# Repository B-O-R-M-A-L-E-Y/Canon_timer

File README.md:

# Canon_timer/Пульт Timelapse съёмки (для фотоаппартов Canon)
Можно настроить интервал между снимками, их количество и выдержку. Файлы печатной платы и схемы в папке timr_canon_pcb (проект в KiCAD). Исходный код в папке Src, имеется также иницализация CubeMX и проект в Keil. Применена библиотека HAL.
### Небольшая инструкция
 - При запуске фотоаппарат необходимо перевести в режим BULB.
 - Подключить пульт (разъем jack 2.5)
 - Настройка параметров осуществляется выбором соответствующего пункта меню. Затем нужно нажать на энкодер, вращением энкодера изменяется численное значение парметра. Для перехода к следующему значению нужно снова нажать на энкодер.
 - Для запуска перейти в пункт Start и нажать на энкодер. Для выхода из этого режима нажать на энкодер в течении 5 сек.

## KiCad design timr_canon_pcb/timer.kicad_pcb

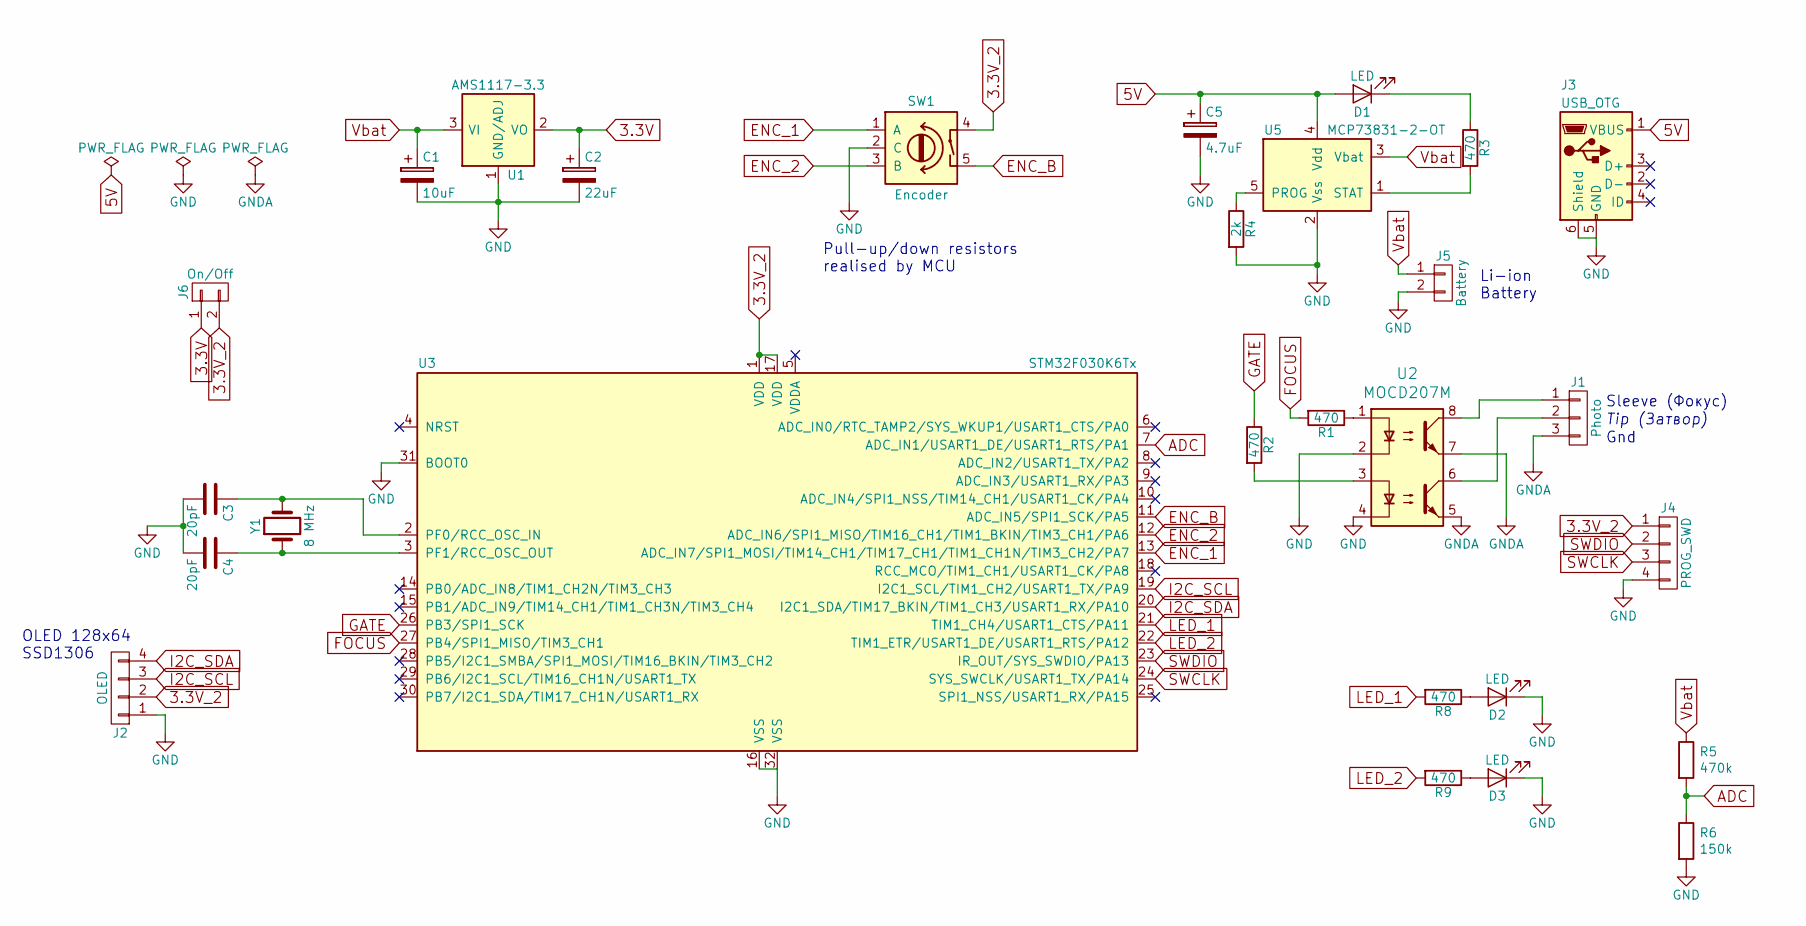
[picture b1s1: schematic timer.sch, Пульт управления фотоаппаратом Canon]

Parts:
C1: 10uF; C_0805_HandSoldering
C2: 22uF; C_0805_HandSoldering
C3, C4: 20pF; C_0805_HandSoldering
C5: 4.7uF; C_0805_HandSoldering
D1, D2, D3: LED; LED_0805
J1: Photo; Pin_Header_Straight_1x03_Pitch2.54mm
J2: OLED; Pin_Header_Straight_1x04_Pitch2.54mm
J3: USB_OTG; USB_Micro-B
J4: PROG_SWD; Pin_Header_Straight_1x04_Pitch2.54mm
J5: Battery; Pin_Header_Straight_1x02_Pitch2.54mm
J6: On/Off; Pin_Header_Straight_1x02_Pitch2.54mm
R1, R2, R3, R8, R9: 470; R_0805_2012Metric_Pad1.15x1.40mm_HandSolder
R4: 2k; R_0805_2012Metric_Pad1.15x1.40mm_HandSolder
R5: 470k; R_0805_2012Metric_Pad1.15x1.40mm_HandSolder
R6: 150k; R_0805_2012Metric_Pad1.15x1.40mm_HandSolder
SW1: Encoder; RotaryEncoder_Alps_EC11E-Switch_Vertical_H20mm
U1: AMS1117-3.3; SOT-223
U2: MOCD207M; SOIC-8_3.9x4.9mm_P1.27mm
U3: STM32F030K6Tx; LQFP-32_7x7mm_Pitch0.8mm
U5: MCP73831-2-OT; SOT-23-5
Y1: 8 MHz; Crystal_HC49-4H_Vertical

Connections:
3.3V: C2.1, J6.1, U1.2 (VO)
3.3V_2: J2.2, J4.1, J6.2, SW1.4, U3.1 (VDD), U3.17 (VDD)
5V: C5.1, D1.2 (A), J3.1 (VBUS), U5.4 (Vdd)
ADC: R5.2, R6.1, U3.7 (ADC_IN1/USART1_DE/USART1_RTS/PA1)
ENC_1: SW1.1 (A), U3.13 (ADC_IN7/SPI1_MOSI/TIM14_CH1/TIM17_CH1/T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)
ENC_2: SW1.3 (B), U3.12 (ADC_IN6/SPI1_MISO/TIM16_CH1/TIM1_BKIN/T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)
ENC_B: SW1.5, U3.11 (ADC_IN5/SPI1_SCK/PA5)
FOCUS: R1.2, U3.27 (PB4/SPI1_MISO/TIM3_CH1)
GATE: R2.1, U3.26 (PB3/SPI1_SCK)
GND: C1.2, C2.2, C3.2, C4.2, C5.2, D2.1 (K), D3.1 (K), J2.1, J3.5 (GND), J3.6 (Shield), J4.4, J5.2, R4.2, R6.2, SW1.2 (C), U1.1 (GND/ADJ), U2.2, U2.4, U3.16 (VSS), U3.31 (BOOT0), U3.32 (VSS), U5.2 (Vss)
GNDA: J1.3, U2.5, U2.7
I2C_SCL: J2.3, U3.19 (I2C1_SCL/TIM1_CH2/USART1_TX/PA9)
I2C_SDA: J2.4, U3.20 (I2C1_SDA/TIM17_BKIN/TIM1_CH3/USART1_RX/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)
LED_1: R8.2, U3.21 (TIM1_CH4/USART1_CTS/PA11)
LED_2: R9.2, U3.22 (TIM1_ETR/USART1_DE/USART1_RTS/PA12)
unnamed: C3.1, U3.2 (PF0/RCC_OSC_IN), Y1.2
unnamed: C4.1, U3.3 (PF1/RCC_OSC_OUT), Y1.1
unnamed: D1.1 (K), R3.1
unnamed: D2.2 (A), R8.1
unnamed: D3.2 (A), R9.1
unnamed: J1.1, U2.8
unnamed: J1.2, U2.6
unnamed: R1.1, U2.1
unnamed: R2.2, U2.3
unnamed: R3.2, U5.1 (STAT)
unnamed: R4.1, U5.5 (PROG)
SWCLK: J4.3, U3.24 (SYS_SWCLK/USART1_TX/PA14)
SWDIO: J4.2, U3.23 (IR_OUT/SYS_SWDIO/PA13)
Vbat: C1.1, J5.1, R5.1, U1.3 (VI), U5.3 (Vbat)

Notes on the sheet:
Tip (Затвор)
Sleeve (Фокус)
Gnd
OLED 128x64 SSD1306
Li-ion Battery
Pull-up/down resistors realised by MCU

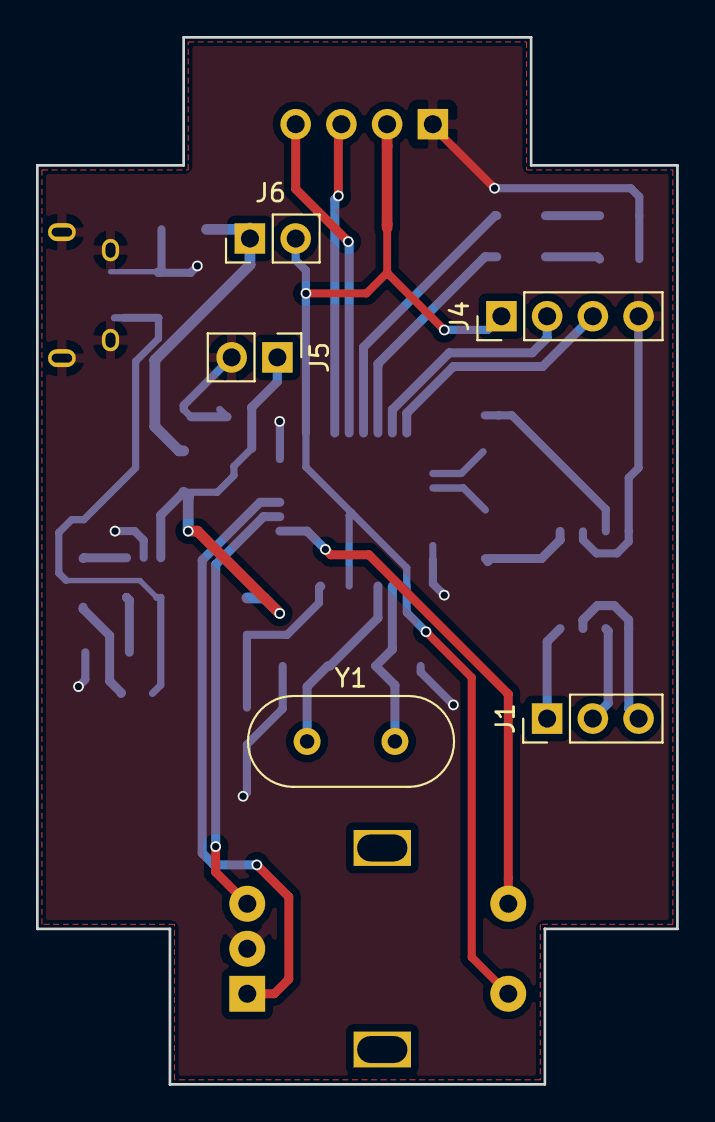
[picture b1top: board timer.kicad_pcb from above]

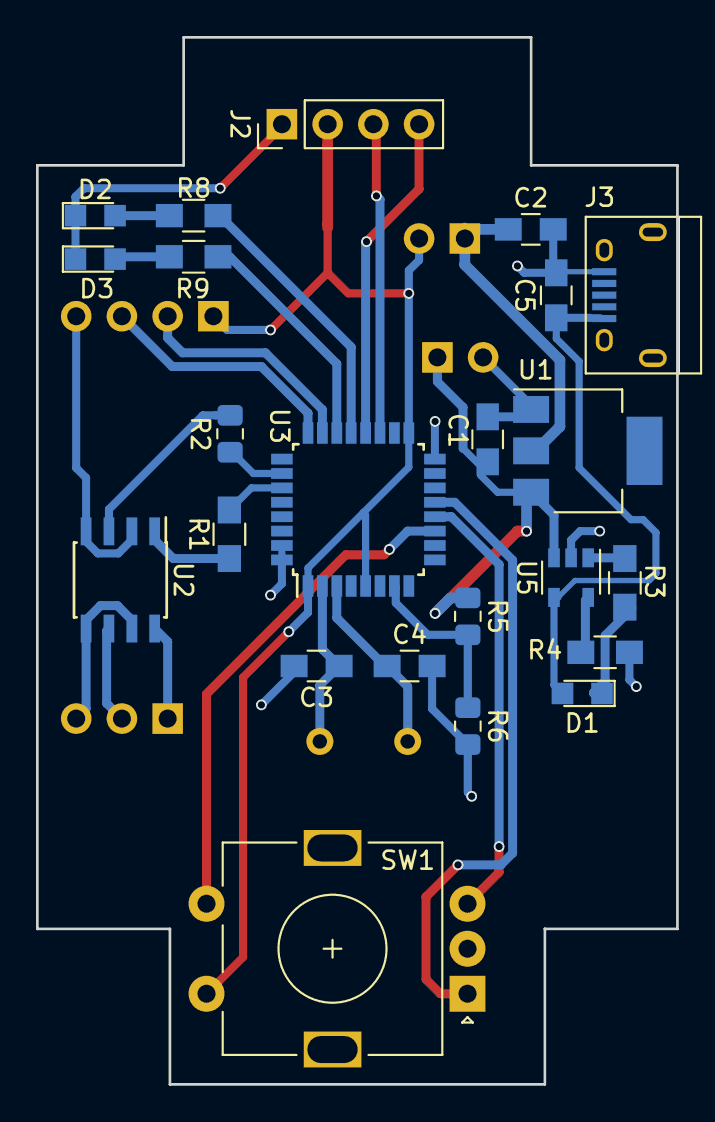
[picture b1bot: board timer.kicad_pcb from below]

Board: 2 copper layers, 35.6 x 58.2 mm, 28 parts (23 on the bottom side), 29 nets.

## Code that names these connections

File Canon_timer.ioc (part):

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Mcu.Name=STM32F030K6Tx
Mcu.Package=LQFP32
Mcu.UserName=STM32F030K6Tx
PA0.Signal=GPIO_Output
PA1.Signal=GPIO_Output
PA10.Mode=I2C
PA10.Signal=I2C1_SDA
PA11.Signal=GPIO_Output
PA12.Signal=GPIO_Output
PA13.Mode=Serial_Wire
PA13.Signal=SYS_SWDIO
PA14.Mode=Serial_Wire
PA14.Signal=SYS_SWCLK
PA5.GPIOParameters=GPIO_PuPd
PA5.GPIO_PuPd=GPIO_PULLDOWN
PA5.Signal=GPIO_Input
PA6.GPIOParameters=GPIO_PuPd
PA6.GPIO_PuPd=GPIO_PULLUP
PA6.Signal=S_TIM3_CH1
PA7.GPIOParameters=GPIO_PuPd
PA7.GPIO_PuPd=GPIO_PULLUP
PA7.Signal=S_TIM3_CH2
PA9.Mode=I2C
PA9.Signal=I2C1_SCL
PF0-OSC_IN.Mode=HSE-External-Oscillator
PF0-OSC_IN.Signal=RCC_OSC_IN
PF1-OSC_OUT.Mode=HSE-External-Oscillator
PF1-OSC_OUT.Signal=RCC_OSC_OUT
RCC.SYSCLKFreq_VALUE=8000000
RCC.SYSCLKSource=RCC_SYSCLKSOURCE_HSE
board=Canon_timer

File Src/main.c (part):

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      HAL_NVIC_EnableIRQ(EXTI4_15_IRQn);

      HAL_GPIO_WritePin(GPIOA, LED_GREEN_PIN|LED_RED_PIN, GPIO_PIN_RESET);
      HAL_GPIO_WritePin(GPIOB, GATE_PIN|FOCUS_PIN, GPIO_PIN_RESET);

      HAL_PWR_EnterSTOPMode(PWR_LOWPOWERREGULATOR_ON, PWR_STOPENTRY_WFE);

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      if(gate_flag)
      {
        // Reset Gate & Focus
        HAL_GPIO_WritePin(GPIOB, FOCUS_PIN|GATE_PIN, GPIO_PIN_RESET);
        HAL_TIM_Base_Stop_IT(&htim14);
        HAL_Delay(500);
        __HAL_TIM_SET_COUNTER(&htim14, 0);
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      HAL_Delay(1000);
      exiting_run = 0;
      HAL_TIM_Base_Start_IT(&htim16);
      HAL_GPIO_WritePin(GPIOB, FOCUS_PIN|GATE_PIN, GPIO_PIN_RESET);
    }   
  }
  /* USER CODE END 3 */
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  /*Configure GPIO pin Output Level */
  HAL_GPIO_WritePin(GPIOA, GPIO_PIN_11|GPIO_PIN_12, GPIO_PIN_RESET);

  /*Configure GPIO pins : PA0 PA1 PA11 PA12 */
  GPIO_InitStruct.Pin = GPIO_PIN_11|GPIO_PIN_12;
  GPIO_InitStruct.Mode = GPIO_MODE_OUTPUT_PP;
  GPIO_InitStruct.Pull = GPIO_NOPULL;
  GPIO_InitStruct.Speed = GPIO_SPEED_FREQ_LOW;
  HAL_GPIO_Init(GPIOA, &GPIO_InitStruct);

  /*Configure GPIO pin : PA5 */
  GPIO_InitStruct.Pin = GPIO_PIN_5;
  GPIO_InitStruct.Mode = GPIO_MODE_INPUT;
  GPIO_InitStruct.Pull = GPIO_PULLDOWN;
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  /*Configure GPIO pin Output Level */
  HAL_GPIO_WritePin(GPIOB, GPIO_PIN_3|GPIO_PIN_4, GPIO_PIN_RESET);
  
  /*Configure GPIO pins : PB3 PB4 */
  GPIO_InitStruct.Pin = GPIO_PIN_3|GPIO_PIN_4;
  GPIO_InitStruct.Mode = GPIO_MODE_OUTPUT_PP;
  GPIO_InitStruct.Pull = GPIO_NOPULL;
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
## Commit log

2018-10-01 Lower current consumption
    Added switching off OLED before going to sleep. Also ssd1306.h now has public WriteCommand function (it was static)
2018-10-04 Refactored code
    New menu, separated minutes and sconds control, also interval mode
2018-10-05 Interval mode
2018-10-08 Exit by holding button for 3s
2018-10-27 could exit from running by holding button
2019-05-29 readme
2019-05-29 add pcb & schematics
2019-05-29 instruction
2019-05-29 instruction 2
2019-08-31 deleted temp files
2019-08-31 cleared tmp files & small changes
2019-09-09 cleaned

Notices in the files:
Src/main.c:
COPYRIGHT(c) 2018 STMicroelectronics
(C) COPYRIGHT STMicroelectronics *****END OF FILE
